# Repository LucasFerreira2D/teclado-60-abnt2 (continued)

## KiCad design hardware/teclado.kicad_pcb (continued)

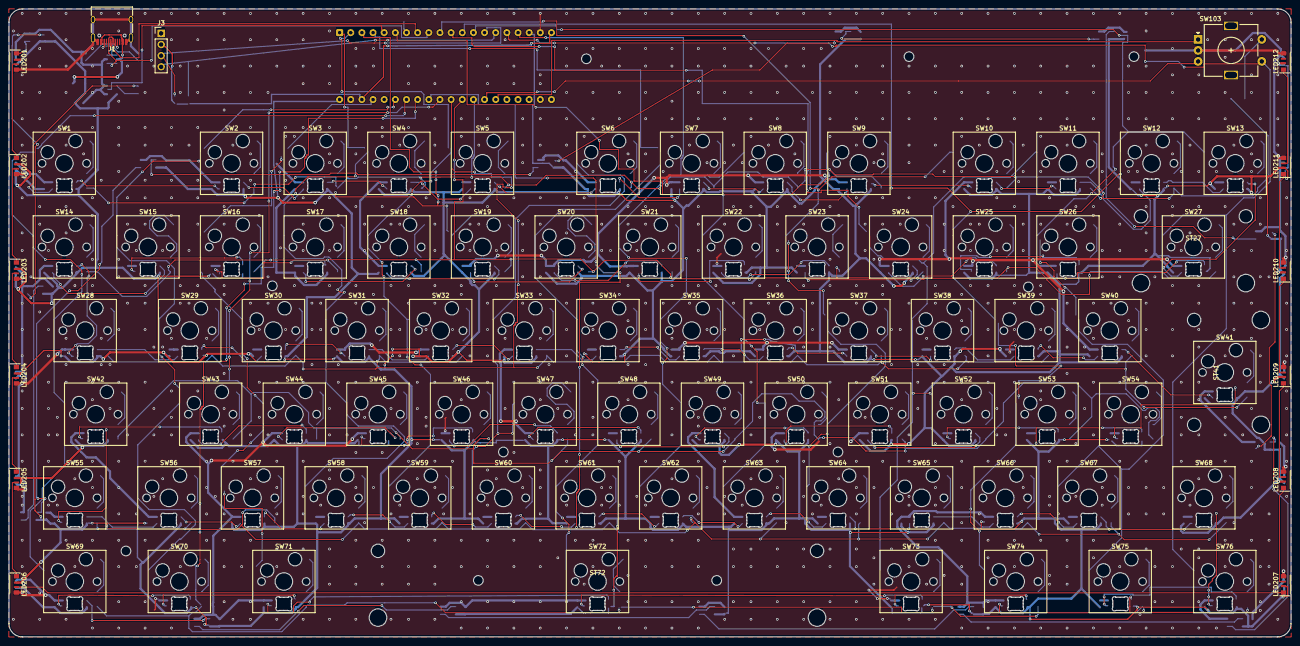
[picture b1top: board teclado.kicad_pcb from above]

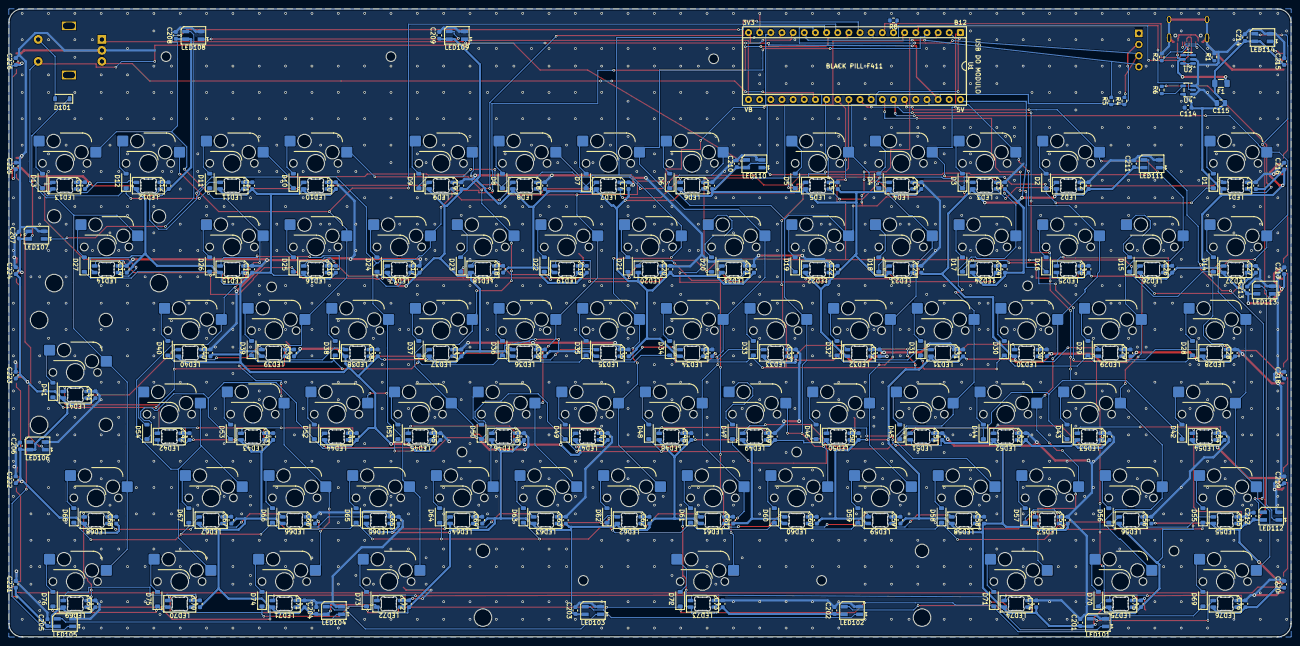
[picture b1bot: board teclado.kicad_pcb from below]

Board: 2 copper layers, 292.0 x 143.0 mm, 385 parts (281 on the bottom side), 214 nets.

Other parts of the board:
H1, H2, H3, H4, H5, H6, H7, H8, H9, H10: M2; MountingHole_2.2mm_M2

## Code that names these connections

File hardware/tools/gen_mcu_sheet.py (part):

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NC = "NC"

# Pinos do módulo fora da matriz:
#   PA10  USART1_RX do bootloader de fábrica: flutuando impede o DFU por USB -> pull-down R8
#   PA0   botão KEY do módulo (liga ao GND quando apertado): fica no encoder, que também fecha para o GND
#   PB2   BOOT1, com pull-down de 10k no módulo; PC13 é o LED do módulo; PC14/PC15 têm o cristal de 32 kHz
COLS = ["PB0", "PB1", "PB10", "PB12", "PB13", "PB14", "PB15", "PB9", "PA9", "PA15", "PB3", "PB4", "PB5", "PB8"]
ROWS = ["PA2", "PA3", "PA4", "PA5", "PA6", "PA7"]

mcu_nets = {
    "5V": P + "+5V", "3V3": P + "+3V3", "GND": P + "GND", "VBAT": NC, "NRST": NC,
    "PA11": LL + "USB_DM", "PA12": LL + "USB_DP",
    "PB6": LL + "I2C_SCL", "PB7": LL + "I2C_SDA", "PA0": LL + "ENC_A", "PA1": LL + "ENC_B", "PA8": LL + "RGB_3V3",
    "PA10": LL + "PA10_PD", "PB2": NC, "PC13": NC, "PC14": NC, "PC15": NC,
}
for i, p in enumerate(ROWS):
    mcu_nets[p] = GL + f"ROW{i}"
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    ("F1", "Device", "Polyfuse", "500mA", "Fuse:Fuse_1206_3216Metric", 142.24, 50.8, 90, {"1": P + "VBUS", "2": P + "+5V"}),
    # --- módulo Black Pill (soquete DIP-40 largo, no verso)
    ("U1", "teclado", "BlackPill_F411", "BlackPill F411 (WeAct V3.x)", None, 203.2, 152.4, 0, mcu_nets),
    ("R8", "Device", "R", "10k", R603, 147.32, 210.82, 0, {"1": LL + "PA10_PD", "2": P + "GND"}),    # PA10 (USART1_RX do bootloader) nunca flutua
    # --- OLED I2C (módulo SSD1306 0.91": GND VCC SCL SDA)
    ("J3", "Connector_Generic", "Conn_01x04", "OLED_I2C", "Connector_PinHeader_2.54mm:PinHeader_1x04_P2.54mm_Vertical", 302.26, 104.14, 0,
     {"1": P + "GND", "2": P + "+3V3", "3": LL + "I2C_SCL", "4": LL + "I2C_SDA"}),
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
MCU_NOTES = [
    (30.48, 40.64, "USB-C, ESD e fusível"), (160.02, 111.76, "Módulo Black Pill STM32F411 (em soquete, no verso)"),
    (129.54, 198.12, "Pull-down PA10 (DFU)"),
    (284.48, 88.9, "OLED I2C"), (284.48, 134.62, "RGB: buffer 3V3 -> 5V (SK6812)"),
    (284.48, 203.2, "Knob EC11: A/B no MCU, clique na matriz (ROW0 x COL13)"),
]
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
